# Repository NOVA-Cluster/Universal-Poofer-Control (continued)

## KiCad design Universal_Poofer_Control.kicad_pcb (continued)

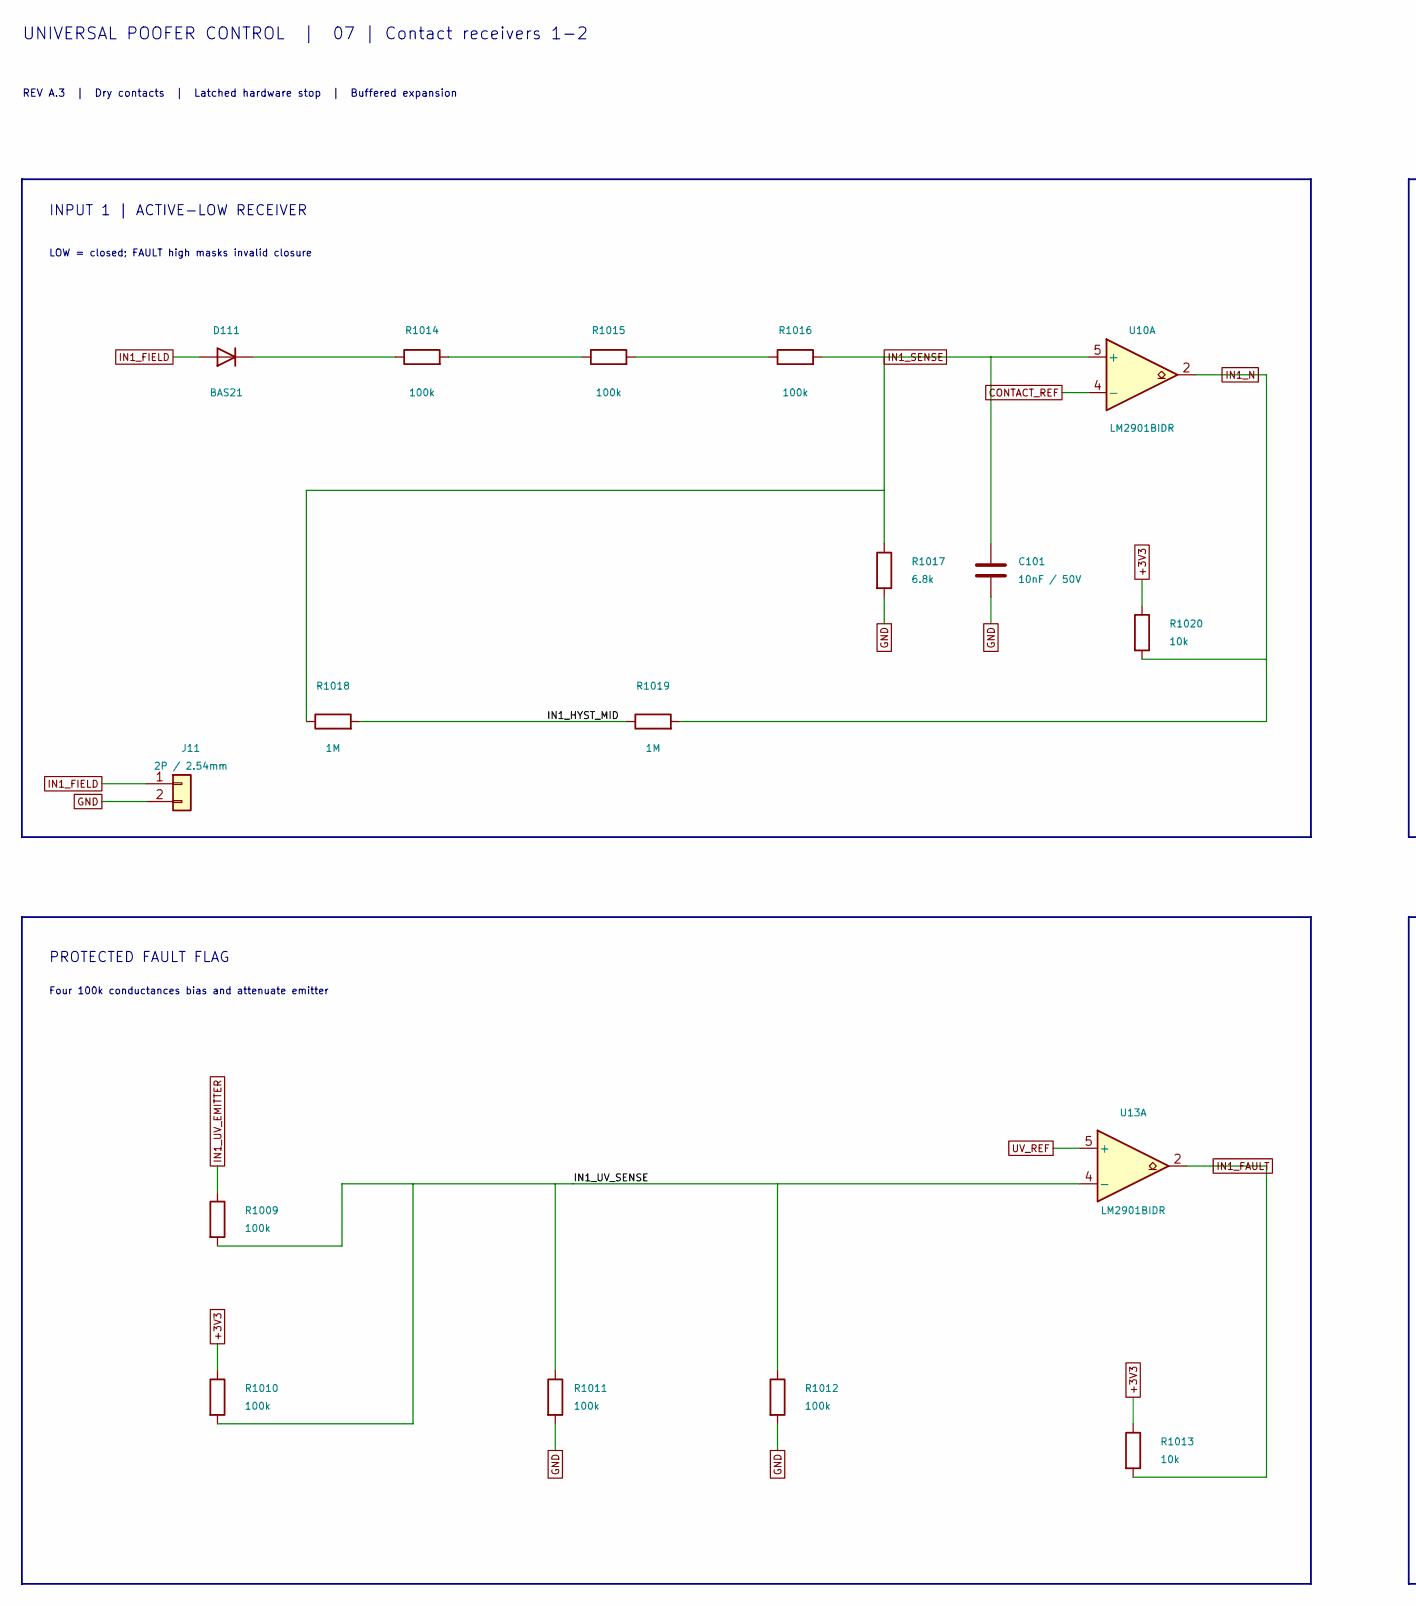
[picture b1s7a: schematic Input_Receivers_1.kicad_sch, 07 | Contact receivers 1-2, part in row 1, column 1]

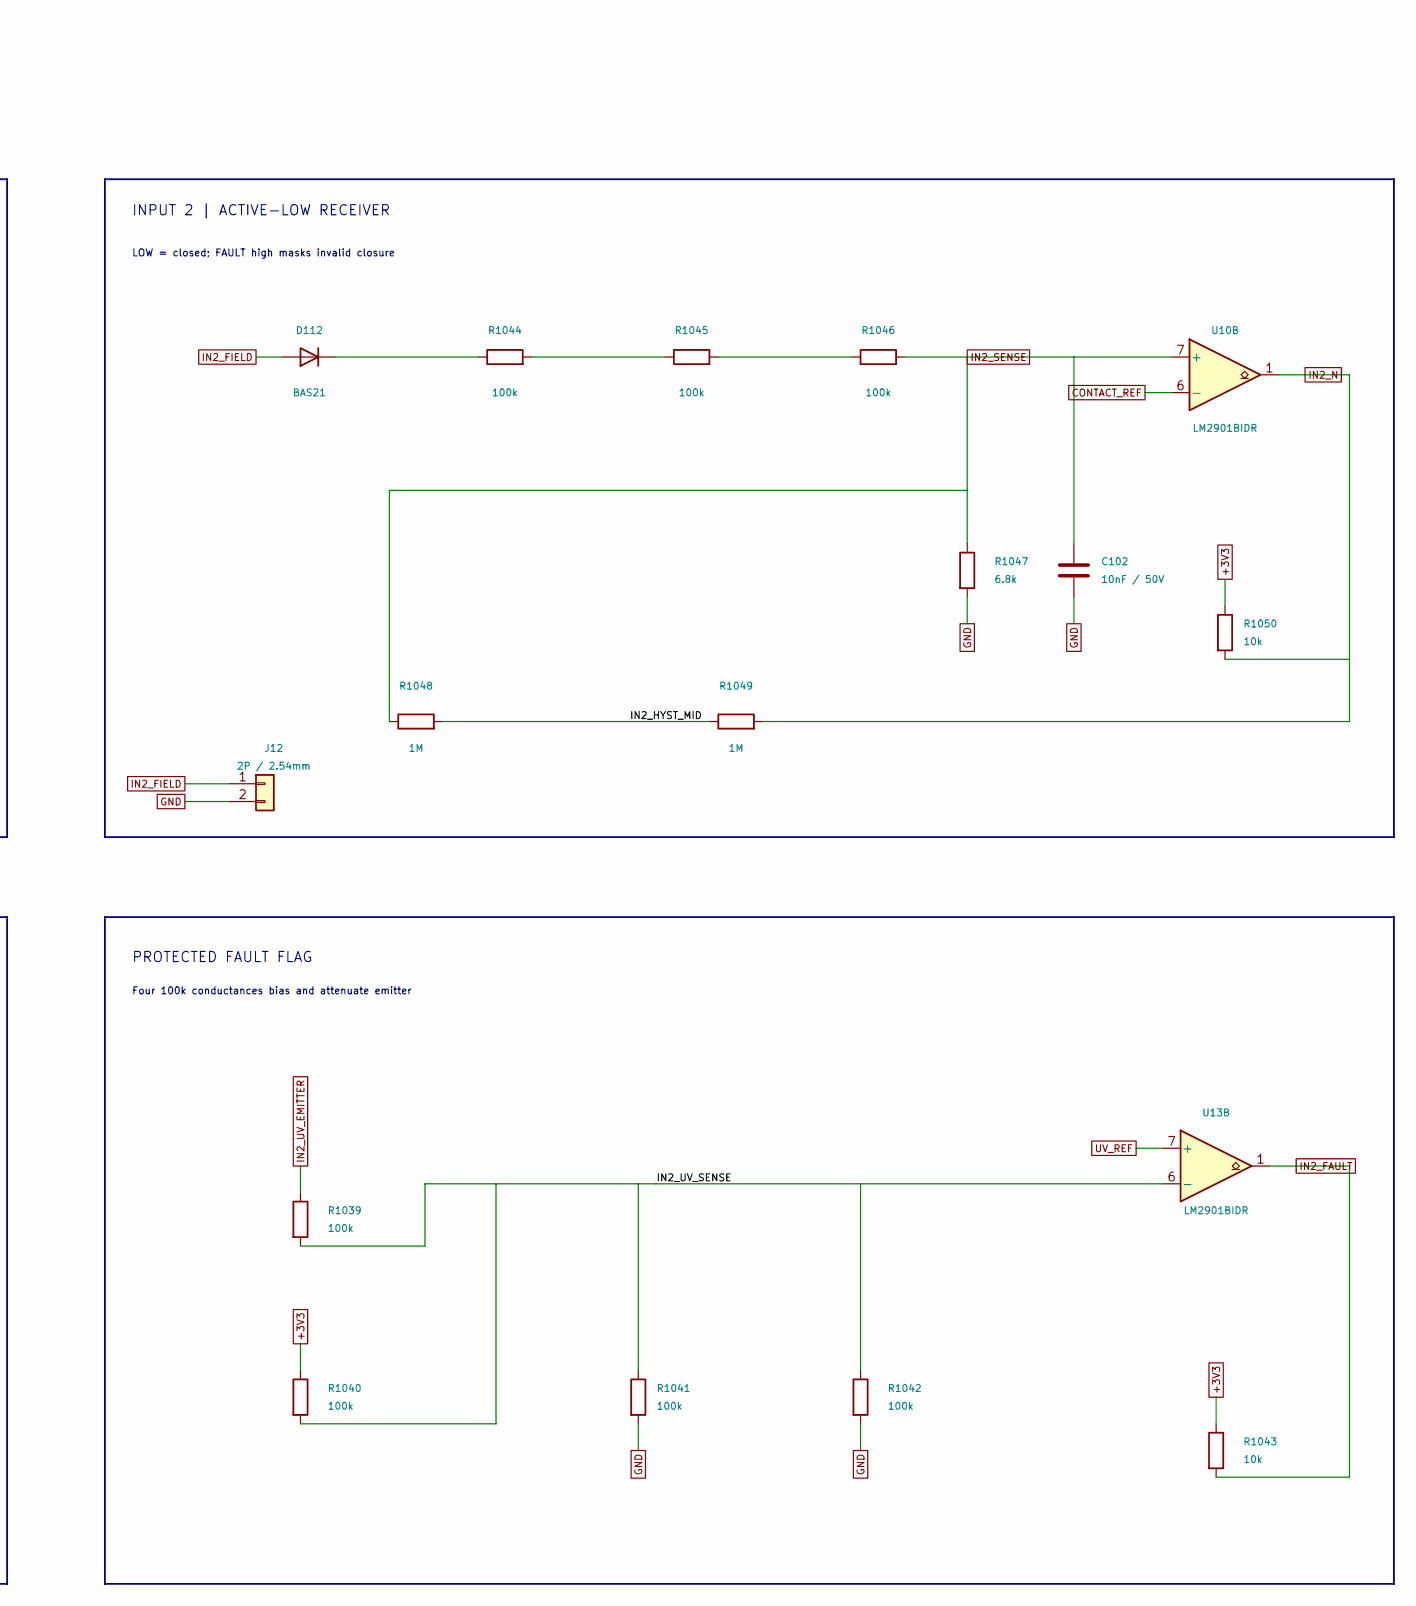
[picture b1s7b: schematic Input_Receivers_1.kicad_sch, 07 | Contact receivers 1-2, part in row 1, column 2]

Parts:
C101, C102: 10nF / 50V; C_0805_2012Metric; MPN CL21B103KBANNNC; LCSC C1710
D111, D112: BAS21; SOT-23; MPN BAS21,215; LCSC C8661
J11, J12: 2P / 2.54mm; PinHeader_1x02_P2.54mm_Vertical; MPN B-2100S02P-A110; LCSC C124375
R1009, R1010, R1011, R1012, R1014, R1015, R1016, R1039, R1040, R1041, R1042, R1044, R1045, R1046: 100k; R_0805_2012Metric; MPN 0805W8F1003T5E; LCSC C149504
R1013, R1020, R1043, R1050: 10k; R_0805_2012Metric; MPN 0805W8F1002T5E; LCSC C17414
R1017, R1047: 6.8k; R_0805_2012Metric; MPN 0805W8F6801T5E; LCSC C17772
R1018, R1019, R1048, R1049: 1M; R_0805_2012Metric; MPN 0805W8F1004T5E; LCSC C17514
U10, U13: LM2901BIDR; SOIC-14_3.9x8.7mm_P1.27mm; MPN LM2901BIDR; LCSC C22427890

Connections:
+3V3: R1010.1, R1013.1, R1020.1, R1040.1, R1043.1, R1050.1; also elsewhere on the board
/07 | Contact receivers 1-2/IN1_HYST_MID: R1018.2, R1019.1
/07 | Contact receivers 1-2/IN1_UV_SENSE: R1009.2, R1010.2, R1011.1, R1012.1, U13.4 (-)
/07 | Contact receivers 1-2/IN2_HYST_MID: R1048.2, R1049.1
/07 | Contact receivers 1-2/IN2_UV_SENSE: R1039.2, R1040.2, R1041.1, R1042.1, U13.6 (-)
CONTACT_REF: U10.4 (-), U10.6 (-); also elsewhere on the board
GND: C101.2, C102.2, J11.2, J12.2, R1011.2, R1012.2, R1017.2, R1041.2, R1042.2, R1047.2; also elsewhere on the board
IN1_FAULT: R1013.2, U13.2; also elsewhere on the board
IN1_FIELD: D111.1 (A), J11.1; also elsewhere on the board
IN1_N: R1019.2, R1020.2, U10.2; also elsewhere on the board
IN1_SENSE: C101.1, R1016.2, R1017.1, R1018.1, U10.5 (+)
IN1_UV_EMITTER: R1009.1; also elsewhere on the board
IN2_FAULT: R1043.2, U13.1; also elsewhere on the board
IN2_FIELD: D112.1 (A), J12.1; also elsewhere on the board
IN2_N: R1049.2, R1050.2, U10.1; also elsewhere on the board
IN2_SENSE: C102.1, R1046.2, R1047.1, R1048.1, U10.7 (+)
IN2_UV_EMITTER: R1039.1; also elsewhere on the board
unnamed: D111.3 (K), R1014.1
unnamed: D112.3 (K), R1044.1
unnamed: R1014.2, R1015.1
unnamed: R1015.2, R1016.1
unnamed: R1044.2, R1045.1
unnamed: R1045.2, R1046.1
UV_REF: U13.5 (+), U13.7 (+); also elsewhere on the board

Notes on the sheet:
UNIVERSAL POOFER CONTROL | 07 | Contact receivers 1-2
REV A.3 | Dry contacts | Latched hardware stop | Buffered expansion
INPUT 1 | ACTIVE-LOW RECEIVER
LOW = closed; FAULT high masks invalid closure
PROTECTED FAULT FLAG
Four 100k conductances bias and attenuate emitter
INPUT 2 | ACTIVE-LOW RECEIVER

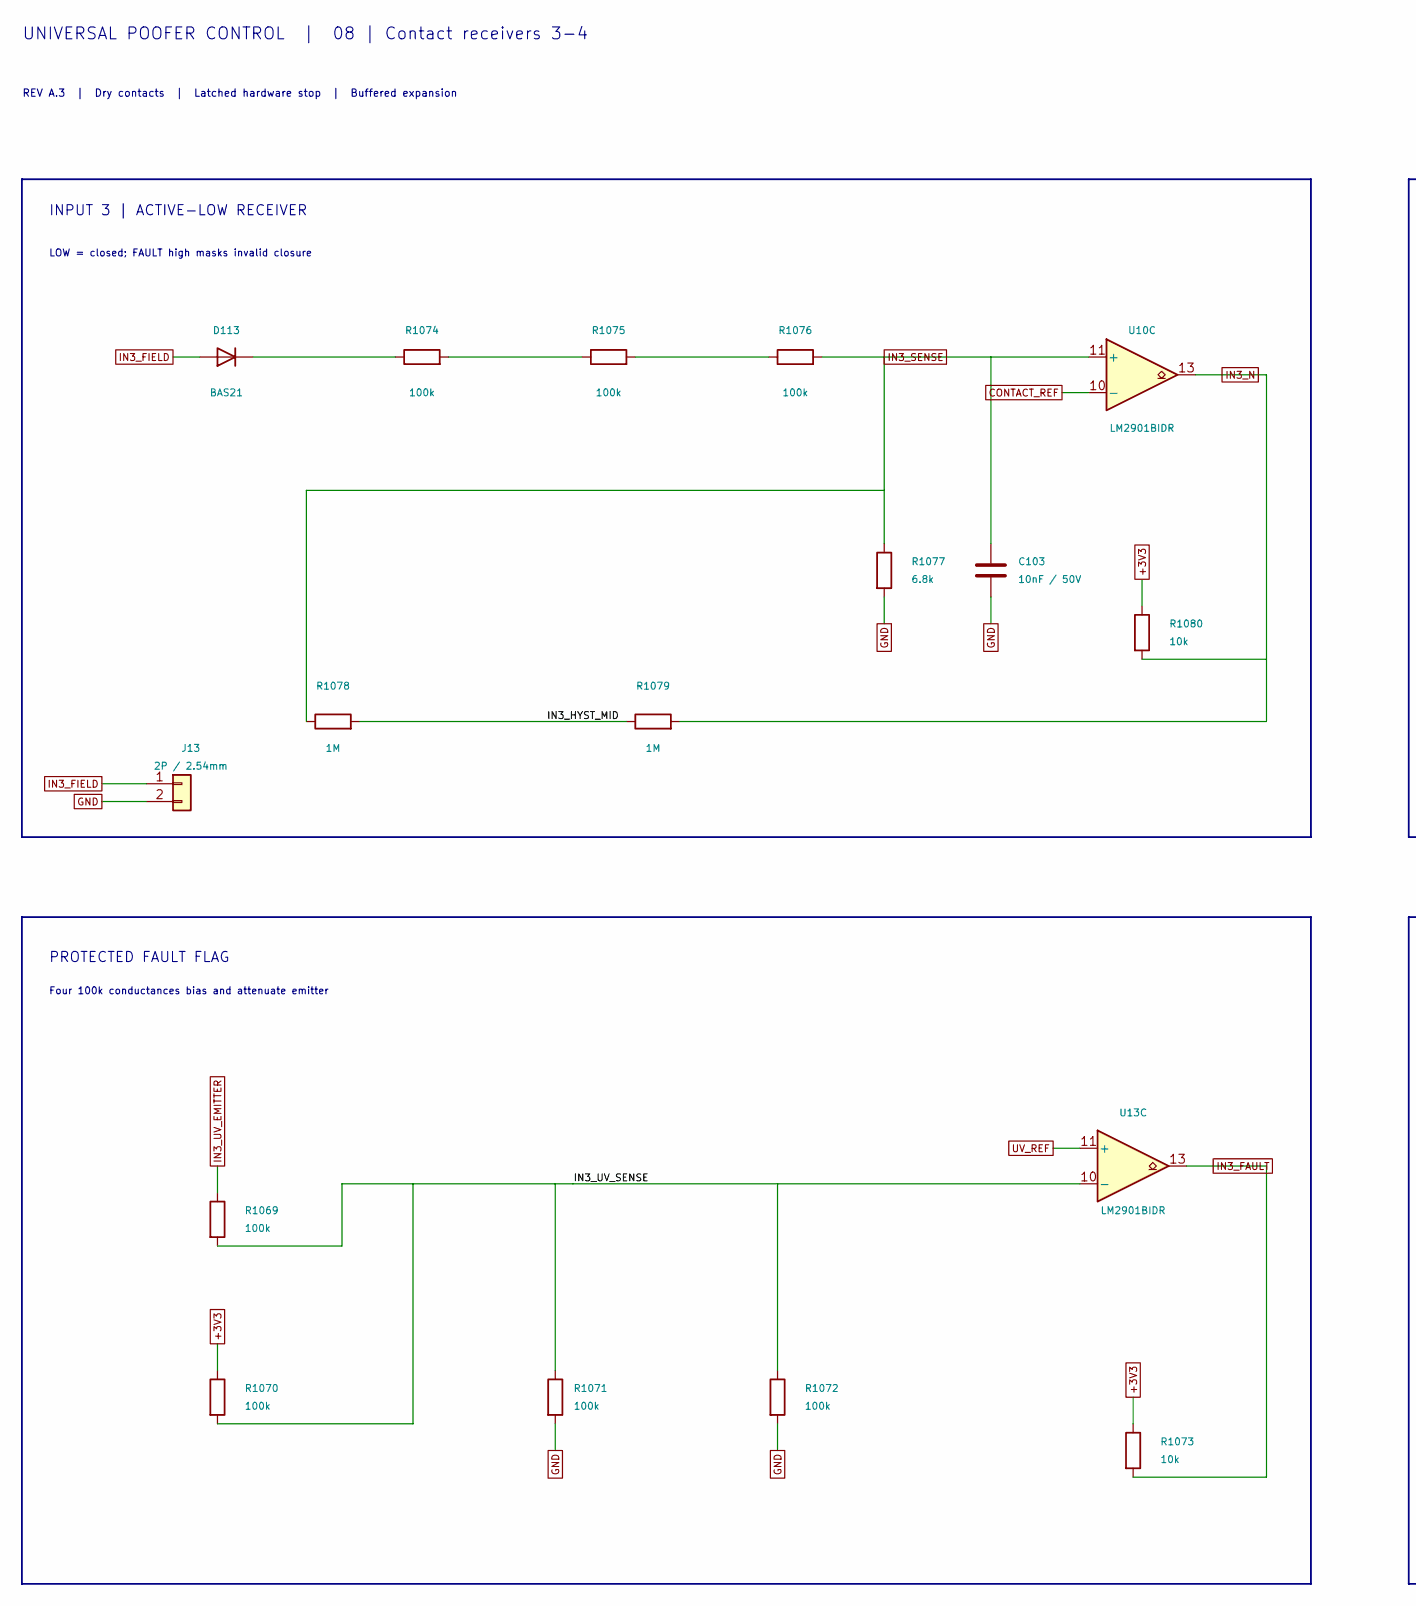
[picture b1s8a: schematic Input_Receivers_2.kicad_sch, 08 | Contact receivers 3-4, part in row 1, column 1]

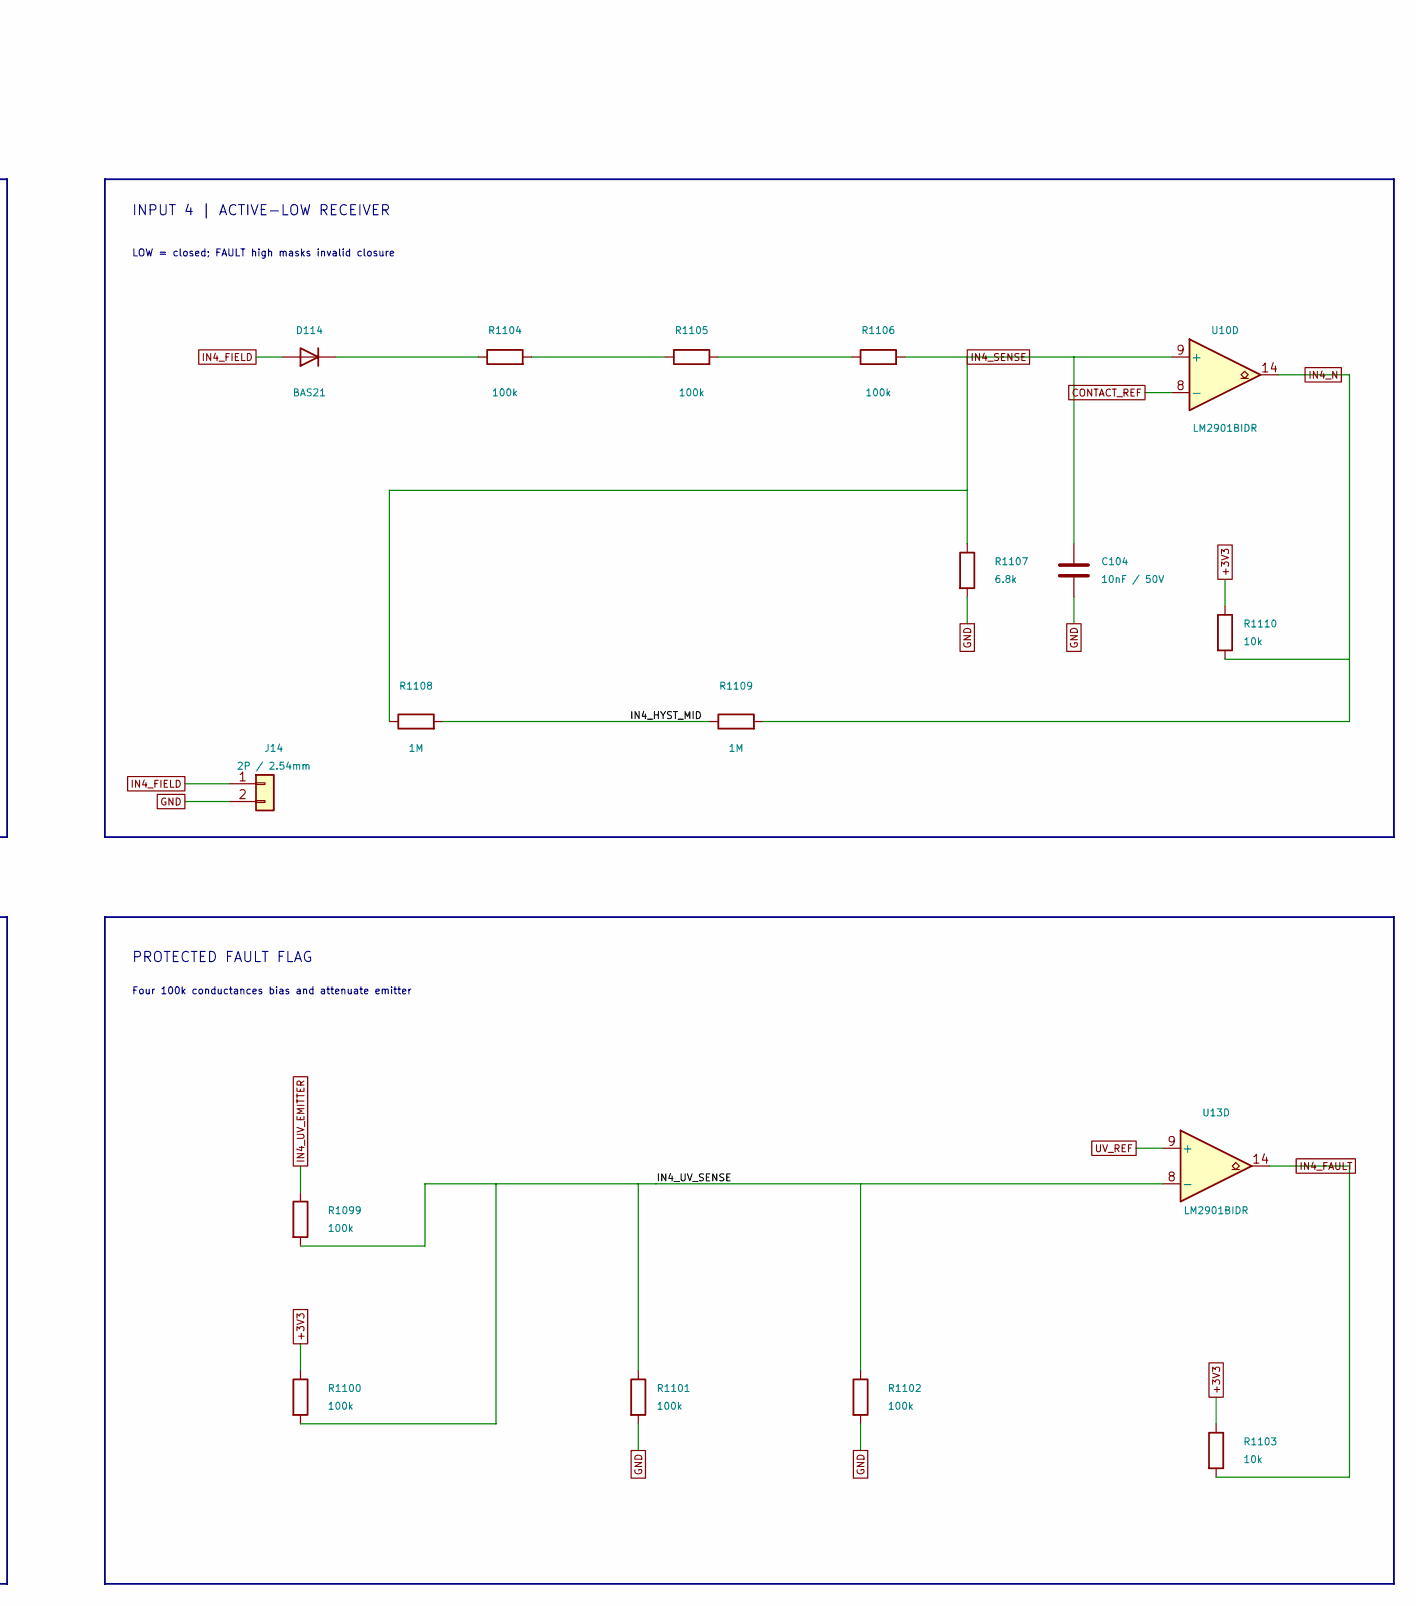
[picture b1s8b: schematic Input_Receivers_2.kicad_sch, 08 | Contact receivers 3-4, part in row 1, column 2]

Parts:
C103, C104: 10nF / 50V; C_0805_2012Metric; MPN CL21B103KBANNNC; LCSC C1710
D113, D114: BAS21; SOT-23; MPN BAS21,215; LCSC C8661
J13, J14: 2P / 2.54mm; PinHeader_1x02_P2.54mm_Vertical; MPN B-2100S02P-A110; LCSC C124375
R1069, R1070, R1071, R1072, R1074, R1075, R1076, R1099, R1100, R1101, R1102, R1104, R1105, R1106: 100k; R_0805_2012Metric; MPN 0805W8F1003T5E; LCSC C149504
R1073, R1080, R1103, R1110: 10k; R_0805_2012Metric; MPN 0805W8F1002T5E; LCSC C17414
R1077, R1107: 6.8k; R_0805_2012Metric; MPN 0805W8F6801T5E; LCSC C17772
R1078, R1079, R1108, R1109: 1M; R_0805_2012Metric; MPN 0805W8F1004T5E; LCSC C17514
U10, U13: LM2901BIDR; SOIC-14_3.9x8.7mm_P1.27mm; MPN LM2901BIDR; LCSC C22427890

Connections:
+3V3: R1070.1, R1073.1, R1080.1, R1100.1, R1103.1, R1110.1; also elsewhere on the board
/08 | Contact receivers 3-4/IN3_HYST_MID: R1078.2, R1079.1
/08 | Contact receivers 3-4/IN3_UV_SENSE: R1069.2, R1070.2, R1071.1, R1072.1, U13.10 (-)
/08 | Contact receivers 3-4/IN4_HYST_MID: R1108.2, R1109.1
/08 | Contact receivers 3-4/IN4_UV_SENSE: R1099.2, R1100.2, R1101.1, R1102.1, U13.8 (-)
CONTACT_REF: U10.8 (-), U10.10 (-); also elsewhere on the board
GND: C103.2, C104.2, J13.2, J14.2, R1071.2, R1072.2, R1077.2, R1101.2, R1102.2, R1107.2; also elsewhere on the board
IN3_FAULT: R1073.2, U13.13; also elsewhere on the board
IN3_FIELD: D113.1 (A), J13.1; also elsewhere on the board
IN3_N: R1079.2, R1080.2, U10.13; also elsewhere on the board
IN3_SENSE: C103.1, R1076.2, R1077.1, R1078.1, U10.11 (+)
IN3_UV_EMITTER: R1069.1; also elsewhere on the board
IN4_FAULT: R1103.2, U13.14; also elsewhere on the board
IN4_FIELD: D114.1 (A), J14.1; also elsewhere on the board
IN4_N: R1109.2, R1110.2, U10.14; also elsewhere on the board
IN4_SENSE: C104.1, R1106.2, R1107.1, R1108.1, U10.9 (+)
IN4_UV_EMITTER: R1099.1; also elsewhere on the board
unnamed: D113.3 (K), R1074.1
unnamed: D114.3 (K), R1104.1
unnamed: R1074.2, R1075.1
unnamed: R1075.2, R1076.1
unnamed: R1104.2, R1105.1
unnamed: R1105.2, R1106.1
UV_REF: U13.9 (+), U13.11 (+); also elsewhere on the board

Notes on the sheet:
UNIVERSAL POOFER CONTROL | 08 | Contact receivers 3-4
REV A.3 | Dry contacts | Latched hardware stop | Buffered expansion
INPUT 3 | ACTIVE-LOW RECEIVER
LOW = closed; FAULT high masks invalid closure
PROTECTED FAULT FLAG
Four 100k conductances bias and attenuate emitter
INPUT 4 | ACTIVE-LOW RECEIVER

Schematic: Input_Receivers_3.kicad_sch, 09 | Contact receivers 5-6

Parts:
C105, C106: 10nF / 50V; C_0805_2012Metric; MPN CL21B103KBANNNC; LCSC C1710
D115, D116: BAS21; SOT-23; MPN BAS21,215; LCSC C8661
J15, J16: 2P / 2.54mm; PinHeader_1x02_P2.54mm_Vertical; MPN B-2100S02P-A110; LCSC C124375
R1129, R1130, R1131, R1132, R1134, R1135, R1136, R1159, R1160, R1161, R1162, R1164, R1165, R1166: 100k; R_0805_2012Metric; MPN 0805W8F1003T5E; LCSC C149504
R1133, R1140, R1163, R1170: 10k; R_0805_2012Metric; MPN 0805W8F1002T5E; LCSC C17414
R1137, R1167: 6.8k; R_0805_2012Metric; MPN 0805W8F6801T5E; LCSC C17772
R1138, R1139, R1168, R1169: 1M; R_0805_2012Metric; MPN 0805W8F1004T5E; LCSC C17514
U11, U14: LM2901BIDR; SOIC-14_3.9x8.7mm_P1.27mm; MPN LM2901BIDR; LCSC C22427890

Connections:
+3V3: R1130.1, R1133.1, R1140.1, R1160.1, R1163.1, R1170.1; also elsewhere on the board
/09 | Contact receivers 5-6/IN5_HYST_MID: R1138.2, R1139.1
/09 | Contact receivers 5-6/IN5_UV_SENSE: R1129.2, R1130.2, R1131.1, R1132.1, U14.4 (-)
/09 | Contact receivers 5-6/IN6_HYST_MID: R1168.2, R1169.1
/09 | Contact receivers 5-6/IN6_UV_SENSE: R1159.2, R1160.2, R1161.1, R1162.1, U14.6 (-)
CONTACT_REF: U11.4 (-), U11.6 (-); also elsewhere on the board
GND: C105.2, C106.2, J15.2, J16.2, R1131.2, R1132.2, R1137.2, R1161.2, R1162.2, R1167.2; also elsewhere on the board
IN5_FAULT: R1133.2, U14.2; also elsewhere on the board
IN5_FIELD: D115.1 (A), J15.1; also elsewhere on the board
IN5_N: R1139.2, R1140.2, U11.2; also elsewhere on the board
IN5_SENSE: C105.1, R1136.2, R1137.1, R1138.1, U11.5 (+)
IN5_UV_EMITTER: R1129.1; also elsewhere on the board
IN6_FAULT: R1163.2, U14.1; also elsewhere on the board
IN6_FIELD: D116.1 (A), J16.1; also elsewhere on the board
IN6_N: R1169.2, R1170.2, U11.1; also elsewhere on the board
IN6_SENSE: C106.1, R1166.2, R1167.1, R1168.1, U11.7 (+)
IN6_UV_EMITTER: R1159.1; also elsewhere on the board
unnamed: D115.3 (K), R1134.1
unnamed: D116.3 (K), R1164.1
unnamed: R1134.2, R1135.1
unnamed: R1135.2, R1136.1
unnamed: R1164.2, R1165.1
unnamed: R1165.2, R1166.1
UV_REF: U14.5 (+), U14.7 (+); also elsewhere on the board

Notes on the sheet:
UNIVERSAL POOFER CONTROL | 09 | Contact receivers 5-6
REV A.3 | Dry contacts | Latched hardware stop | Buffered expansion
INPUT 5 | ACTIVE-LOW RECEIVER
LOW = closed; FAULT high masks invalid closure
PROTECTED FAULT FLAG
Four 100k conductances bias and attenuate emitter
INPUT 6 | ACTIVE-LOW RECEIVER

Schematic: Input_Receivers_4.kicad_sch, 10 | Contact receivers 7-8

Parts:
C107, C108: 10nF / 50V; C_0805_2012Metric; MPN CL21B103KBANNNC; LCSC C1710
D117, D118: BAS21; SOT-23; MPN BAS21,215; LCSC C8661
J17, J18: 2P / 2.54mm; PinHeader_1x02_P2.54mm_Vertical; MPN B-2100S02P-A110; LCSC C124375
R1189, R1190, R1191, R1192, R1194, R1195, R1196, R1219, R1220, R1221, R1222, R1224, R1225, R1226: 100k; R_0805_2012Metric; MPN 0805W8F1003T5E; LCSC C149504
R1193, R1200, R1223, R1230: 10k; R_0805_2012Metric; MPN 0805W8F1002T5E; LCSC C17414
R1197, R1227: 6.8k; R_0805_2012Metric; MPN 0805W8F6801T5E; LCSC C17772
R1198, R1199, R1228, R1229: 1M; R_0805_2012Metric; MPN 0805W8F1004T5E; LCSC C17514
U11, U14: LM2901BIDR; SOIC-14_3.9x8.7mm_P1.27mm; MPN LM2901BIDR; LCSC C22427890

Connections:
+3V3: R1190.1, R1193.1, R1200.1, R1220.1, R1223.1, R1230.1; also elsewhere on the board
/10 | Contact receivers 7-8/IN7_HYST_MID: R1198.2, R1199.1
/10 | Contact receivers 7-8/IN7_UV_SENSE: R1189.2, R1190.2, R1191.1, R1192.1, U14.10 (-)
/10 | Contact receivers 7-8/IN8_HYST_MID: R1228.2, R1229.1
/10 | Contact receivers 7-8/IN8_UV_SENSE: R1219.2, R1220.2, R1221.1, R1222.1, U14.8 (-)
CONTACT_REF: U11.8 (-), U11.10 (-); also elsewhere on the board
GND: C107.2, C108.2, J17.2, J18.2, R1191.2, R1192.2, R1197.2, R1221.2, R1222.2, R1227.2; also elsewhere on the board
IN7_FAULT: R1193.2, U14.13; also elsewhere on the board
IN7_FIELD: D117.1 (A), J17.1; also elsewhere on the board
IN7_N: R1199.2, R1200.2, U11.13; also elsewhere on the board
IN7_SENSE: C107.1, R1196.2, R1197.1, R1198.1, U11.11 (+)
IN7_UV_EMITTER: R1189.1; also elsewhere on the board
IN8_FAULT: R1223.2, U14.14; also elsewhere on the board
IN8_FIELD: D118.1 (A), J18.1; also elsewhere on the board
IN8_N: R1229.2, R1230.2, U11.14; also elsewhere on the board
IN8_SENSE: C108.1, R1226.2, R1227.1, R1228.1, U11.9 (+)
IN8_UV_EMITTER: R1219.1; also elsewhere on the board
unnamed: D117.3 (K), R1194.1
unnamed: D118.3 (K), R1224.1
unnamed: R1194.2, R1195.1
unnamed: R1195.2, R1196.1
unnamed: R1224.2, R1225.1
unnamed: R1225.2, R1226.1
UV_REF: U14.9 (+), U14.11 (+); also elsewhere on the board

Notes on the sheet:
UNIVERSAL POOFER CONTROL | 10 | Contact receivers 7-8
REV A.3 | Dry contacts | Latched hardware stop | Buffered expansion
INPUT 7 | ACTIVE-LOW RECEIVER
LOW = closed; FAULT high masks invalid closure
PROTECTED FAULT FLAG
Four 100k conductances bias and attenuate emitter
INPUT 8 | ACTIVE-LOW RECEIVER

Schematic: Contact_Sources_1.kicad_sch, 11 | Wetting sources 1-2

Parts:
C131, C132: 100nF; C_0805_2012Metric; MPN CC0805KRX7R9BB104; LCSC C49678
C161, C162: 1nF / 50V; C_0805_2012Metric; MPN CL21B102KBANNNC; LCSC C51210
D101, D102, D121, D122: BAS21; SOT-23; MPN BAS21,215; LCSC C8661
D141, D142: BAT54; SOT-23; MPN BAT54,215; LCSC C85084
Q101, Q102: MJD350T4G; TO-252-3_TabPin2; MPN MJD350T4G; LCSC C145514
Q111, Q112, Q121, Q122: MMBT3904; SOT-23; MPN MMBT3904(RANGE:100-300); LCSC C20526
Q131, Q132: AO3401A; SOT-23; MPN AO3401A; LCSC C15127
Q151, Q152: MMBT3906; SOT-23; MPN MMBT3906 2A(RANGE:100-300); LCSC C2143
R1000, R1030: 33R; R_0805_2012Metric; MPN 0805W8F330JT5E; LCSC C17634
R1001, R1031: 2.2k; R_0805_2012Metric; MPN 0805W8F2201T5E; LCSC C17520
R1002, R1003, R1022, R1023, R1032, R1033, R1052, R1053: 1k; R_0805_2012Metric; MPN 0805W8F1001T5E; LCSC C17513
R1004, R1005, R1006, R1007, R1034, R1035, R1036, R1037: 100k; R_0805_2012Metric; MPN 0805W8F1003T5E; LCSC C149504
R1008, R1038: 68k; R_0805_2012Metric; MPN 0805W8F6802T5E; LCSC C17801
R1021, R1051: 10k; R_0805_2012Metric; MPN 0805W8F1002T5E; LCSC C17414
U20: LM2902DR; SOIC-14_3.9x8.7mm_P1.27mm; MPN LM2902DR; LCSC C350545

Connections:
+5V_LOGIC: Q131.2 (S), Q132.2 (S), Q151.2 (E), Q152.2 (E), R1000.1, R1003.1, R1008.1, R1022.1, R1030.1, R1033.1, R1038.1, R1052.1; also elsewhere on the board
/11 | Wetting sources 1-2/IN1_AMP_OUT: C131.1, R1001.2, U20.1
/11 | Wetting sources 1-2/IN1_DRV_BASE: Q111.1 (B), R1001.1
/11 | Wetting sources 1-2/IN1_DRV_COL: Q111.3 (C), R1002.2
/11 | Wetting sources 1-2/IN1_UV_GATE: Q121.3 (C), Q131.1 (G), R1008.2
/11 | Wetting sources 1-2/IN1_WET_COLLECTOR: D101.1 (A), Q101.2 (C)
/11 | Wetting sources 1-2/IN2_AMP_OUT: C132.1, R1031.2, U20.7
/11 | Wetting sources 1-2/IN2_DRV_BASE: Q112.1 (B), R1031.1
/11 | Wetting sources 1-2/IN2_DRV_COL: Q112.3 (C), R1032.2
/11 | Wetting sources 1-2/IN2_UV_GATE: Q122.3 (C), Q132.1 (G), R1038.2
/11 | Wetting sources 1-2/IN2_WET_COLLECTOR: D102.1 (A), Q102.2 (C)
CURRENT_REF: D141.1 (A), D142.1 (A), R1021.1, R1051.1; also elsewhere on the board
GND: C161.2, C162.2, Q111.2 (E), Q112.2 (E), Q121.1 (B), Q122.1 (B), R1007.2, R1037.2; also elsewhere on the board
IN1_AMP_REF: C131.2, D141.3 (K), R1021.2, U20.2 (-)
IN1_EMIT_F: U20.3 (+); also elsewhere on the board
IN1_FIELD: D101.3 (K), D121.3 (K); also elsewhere on the board
IN1_LIMIT_BASE: Q151.1 (B), R1022.2, R1023.1
IN1_UV_EMITTER: C161.1, Q121.2 (E), R1004.1, R1007.1; also elsewhere on the board
IN1_WET_BASE: Q101.1 (B), Q131.3 (D), Q151.3 (C), R1002.1, R1003.2
IN1_WET_EMIT: Q101.3 (E), R1000.2, R1023.2; also elsewhere on the board
IN2_AMP_REF: C132.2, D142.3 (K), R1051.2, U20.6 (-)
IN2_EMIT_F: U20.5 (+); also elsewhere on the board
IN2_FIELD: D102.3 (K), D122.3 (K); also elsewhere on the board
IN2_LIMIT_BASE: Q152.1 (B), R1052.2, R1053.1
IN2_UV_EMITTER: C162.1, Q122.2 (E), R1034.1, R1037.1; also elsewhere on the board
IN2_WET_BASE: Q102.1 (B), Q132.3 (D), Q152.3 (C), R1032.1, R1033.2
IN2_WET_EMIT: Q102.3 (E), R1030.2, R1053.2; also elsewhere on the board
unnamed: D121.1 (A), R1006.2
unnamed: D122.1 (A), R1036.2
unnamed: R1004.2, R1005.1
unnamed: R1005.2, R1006.1
unnamed: R1034.2, R1035.1
unnamed: R1035.2, R1036.1

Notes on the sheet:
UNIVERSAL POOFER CONTROL | 11 | Wetting sources 1-2
REV A.3 | Dry contacts | Latched hardware stop | Buffered expansion
INPUT 1 | PRECISION WETTING SOURCE
Nominal 20 mA; compensated servo and backup limiter
AUTONOMOUS NEGATIVE-FAULT CLAMP
INPUT 2 | PRECISION WETTING SOURCE

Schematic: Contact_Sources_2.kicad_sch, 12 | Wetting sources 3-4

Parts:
C133, C134: 100nF; C_0805_2012Metric; MPN CC0805KRX7R9BB104; LCSC C49678
C163, C164: 1nF / 50V; C_0805_2012Metric; MPN CL21B102KBANNNC; LCSC C51210
D103, D104, D123, D124: BAS21; SOT-23; MPN BAS21,215; LCSC C8661
D143, D144: BAT54; SOT-23; MPN BAT54,215; LCSC C85084
Q103, Q104: MJD350T4G; TO-252-3_TabPin2; MPN MJD350T4G; LCSC C145514
Q113, Q114, Q123, Q124: MMBT3904; SOT-23; MPN MMBT3904(RANGE:100-300); LCSC C20526
Q133, Q134: AO3401A; SOT-23; MPN AO3401A; LCSC C15127
Q153, Q154: MMBT3906; SOT-23; MPN MMBT3906 2A(RANGE:100-300); LCSC C2143
R1060, R1090: 33R; R_0805_2012Metric; MPN 0805W8F330JT5E; LCSC C17634
R1061, R1091: 2.2k; R_0805_2012Metric; MPN 0805W8F2201T5E; LCSC C17520
R1062, R1063, R1082, R1083, R1092, R1093, R1112, R1113: 1k; R_0805_2012Metric; MPN 0805W8F1001T5E; LCSC C17513
R1064, R1065, R1066, R1067, R1094, R1095, R1096, R1097: 100k; R_0805_2012Metric; MPN 0805W8F1003T5E; LCSC C149504
R1068, R1098: 68k; R_0805_2012Metric; MPN 0805W8F6802T5E; LCSC C17801
R1081, R1111: 10k; R_0805_2012Metric; MPN 0805W8F1002T5E; LCSC C17414
U20: LM2902DR; SOIC-14_3.9x8.7mm_P1.27mm; MPN LM2902DR; LCSC C350545

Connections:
+5V_LOGIC: Q133.2 (S), Q134.2 (S), Q153.2 (E), Q154.2 (E), R1060.1, R1063.1, R1068.1, R1082.1, R1090.1, R1093.1, R1098.1, R1112.1; also elsewhere on the board
/12 | Wetting sources 3-4/IN3_AMP_OUT: C133.1, R1061.2, U20.8
/12 | Wetting sources 3-4/IN3_DRV_BASE: Q113.1 (B), R1061.1
/12 | Wetting sources 3-4/IN3_DRV_COL: Q113.3 (C), R1062.2
/12 | Wetting sources 3-4/IN3_UV_GATE: Q123.3 (C), Q133.1 (G), R1068.2
/12 | Wetting sources 3-4/IN3_WET_COLLECTOR: D103.1 (A), Q103.2 (C)
/12 | Wetting sources 3-4/IN4_AMP_OUT: C134.1, R1091.2, U20.14
/12 | Wetting sources 3-4/IN4_DRV_BASE: Q114.1 (B), R1091.1
/12 | Wetting sources 3-4/IN4_DRV_COL: Q114.3 (C), R1092.2
/12 | Wetting sources 3-4/IN4_UV_GATE: Q124.3 (C), Q134.1 (G), R1098.2
/12 | Wetting sources 3-4/IN4_WET_COLLECTOR: D104.1 (A), Q104.2 (C)
CURRENT_REF: D143.1 (A), D144.1 (A), R1081.1, R1111.1; also elsewhere on the board
GND: C163.2, C164.2, Q113.2 (E), Q114.2 (E), Q123.1 (B), Q124.1 (B), R1067.2, R1097.2; also elsewhere on the board
IN3_AMP_REF: C133.2, D143.3 (K), R1081.2, U20.9 (-)
IN3_EMIT_F: U20.10 (+); also elsewhere on the board
IN3_FIELD: D103.3 (K), D123.3 (K); also elsewhere on the board
IN3_LIMIT_BASE: Q153.1 (B), R1082.2, R1083.1
IN3_UV_EMITTER: C163.1, Q123.2 (E), R1064.1, R1067.1; also elsewhere on the board
IN3_WET_BASE: Q103.1 (B), Q133.3 (D), Q153.3 (C), R1062.1, R1063.2
IN3_WET_EMIT: Q103.3 (E), R1060.2, R1083.2; also elsewhere on the board
IN4_AMP_REF: C134.2, D144.3 (K), R1111.2, U20.13 (-)
IN4_EMIT_F: U20.12 (+); also elsewhere on the board
IN4_FIELD: D104.3 (K), D124.3 (K); also elsewhere on the board
IN4_LIMIT_BASE: Q154.1 (B), R1112.2, R1113.1
IN4_UV_EMITTER: C164.1, Q124.2 (E), R1094.1, R1097.1; also elsewhere on the board
IN4_WET_BASE: Q104.1 (B), Q134.3 (D), Q154.3 (C), R1092.1, R1093.2
IN4_WET_EMIT: Q104.3 (E), R1090.2, R1113.2; also elsewhere on the board
unnamed: D123.1 (A), R1066.2
unnamed: D124.1 (A), R1096.2
unnamed: R1064.2, R1065.1
unnamed: R1065.2, R1066.1
unnamed: R1094.2, R1095.1
unnamed: R1095.2, R1096.1

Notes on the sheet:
UNIVERSAL POOFER CONTROL | 12 | Wetting sources 3-4
REV A.3 | Dry contacts | Latched hardware stop | Buffered expansion
INPUT 3 | PRECISION WETTING SOURCE
Nominal 20 mA; compensated servo and backup limiter
AUTONOMOUS NEGATIVE-FAULT CLAMP
INPUT 4 | PRECISION WETTING SOURCE

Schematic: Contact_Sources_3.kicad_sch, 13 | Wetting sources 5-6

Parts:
C135, C136: 100nF; C_0805_2012Metric; MPN CC0805KRX7R9BB104; LCSC C49678
C165, C166: 1nF / 50V; C_0805_2012Metric; MPN CL21B102KBANNNC; LCSC C51210
D105, D106, D125, D126: BAS21; SOT-23; MPN BAS21,215; LCSC C8661
D145, D146: BAT54; SOT-23; MPN BAT54,215; LCSC C85084
Q105, Q106: MJD350T4G; TO-252-3_TabPin2; MPN MJD350T4G; LCSC C145514
Q115, Q116, Q125, Q126: MMBT3904; SOT-23; MPN MMBT3904(RANGE:100-300); LCSC C20526
Q135, Q136: AO3401A; SOT-23; MPN AO3401A; LCSC C15127
Q155, Q156: MMBT3906; SOT-23; MPN MMBT3906 2A(RANGE:100-300); LCSC C2143
R1120, R1150: 33R; R_0805_2012Metric; MPN 0805W8F330JT5E; LCSC C17634
R1121, R1151: 2.2k; R_0805_2012Metric; MPN 0805W8F2201T5E; LCSC C17520
R1122, R1123, R1142, R1143, R1152, R1153, R1172, R1173: 1k; R_0805_2012Metric; MPN 0805W8F1001T5E; LCSC C17513
R1124, R1125, R1126, R1127, R1154, R1155, R1156, R1157: 100k; R_0805_2012Metric; MPN 0805W8F1003T5E; LCSC C149504
R1128, R1158: 68k; R_0805_2012Metric; MPN 0805W8F6802T5E; LCSC C17801
R1141, R1171: 10k; R_0805_2012Metric; MPN 0805W8F1002T5E; LCSC C17414
U21: LM2902DR; SOIC-14_3.9x8.7mm_P1.27mm; MPN LM2902DR; LCSC C350545

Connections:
+5V_LOGIC: Q135.2 (S), Q136.2 (S), Q155.2 (E), Q156.2 (E), R1120.1, R1123.1, R1128.1, R1142.1, R1150.1, R1153.1, R1158.1, R1172.1; also elsewhere on the board
/13 | Wetting sources 5-6/IN5_AMP_OUT: C135.1, R1121.2, U21.1
/13 | Wetting sources 5-6/IN5_DRV_BASE: Q115.1 (B), R1121.1
/13 | Wetting sources 5-6/IN5_DRV_COL: Q115.3 (C), R1122.2
/13 | Wetting sources 5-6/IN5_UV_GATE: Q125.3 (C), Q135.1 (G), R1128.2
/13 | Wetting sources 5-6/IN5_WET_COLLECTOR: D105.1 (A), Q105.2 (C)
/13 | Wetting sources 5-6/IN6_AMP_OUT: C136.1, R1151.2, U21.7
/13 | Wetting sources 5-6/IN6_DRV_BASE: Q116.1 (B), R1151.1
/13 | Wetting sources 5-6/IN6_DRV_COL: Q116.3 (C), R1152.2
/13 | Wetting sources 5-6/IN6_UV_GATE: Q126.3 (C), Q136.1 (G), R1158.2
/13 | Wetting sources 5-6/IN6_WET_COLLECTOR: D106.1 (A), Q106.2 (C)
CURRENT_REF: D145.1 (A), D146.1 (A), R1141.1, R1171.1; also elsewhere on the board
GND: C165.2, C166.2, Q115.2 (E), Q116.2 (E), Q125.1 (B), Q126.1 (B), R1127.2, R1157.2; also elsewhere on the board
IN5_AMP_REF: C135.2, D145.3 (K), R1141.2, U21.2 (-)
IN5_EMIT_F: U21.3 (+); also elsewhere on the board
IN5_FIELD: D105.3 (K), D125.3 (K); also elsewhere on the board
IN5_LIMIT_BASE: Q155.1 (B), R1142.2, R1143.1
IN5_UV_EMITTER: C165.1, Q125.2 (E), R1124.1, R1127.1; also elsewhere on the board
IN5_WET_BASE: Q105.1 (B), Q135.3 (D), Q155.3 (C), R1122.1, R1123.2
IN5_WET_EMIT: Q105.3 (E), R1120.2, R1143.2; also elsewhere on the board
IN6_AMP_REF: C136.2, D146.3 (K), R1171.2, U21.6 (-)
IN6_EMIT_F: U21.5 (+); also elsewhere on the board
IN6_FIELD: D106.3 (K), D126.3 (K); also elsewhere on the board
IN6_LIMIT_BASE: Q156.1 (B), R1172.2, R1173.1
IN6_UV_EMITTER: C166.1, Q126.2 (E), R1154.1, R1157.1; also elsewhere on the board
IN6_WET_BASE: Q106.1 (B), Q136.3 (D), Q156.3 (C), R1152.1, R1153.2
IN6_WET_EMIT: Q106.3 (E), R1150.2, R1173.2; also elsewhere on the board
unnamed: D125.1 (A), R1126.2
unnamed: D126.1 (A), R1156.2
unnamed: R1124.2, R1125.1
unnamed: R1125.2, R1126.1
unnamed: R1154.2, R1155.1
unnamed: R1155.2, R1156.1

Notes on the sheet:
UNIVERSAL POOFER CONTROL | 13 | Wetting sources 5-6
REV A.3 | Dry contacts | Latched hardware stop | Buffered expansion
INPUT 5 | PRECISION WETTING SOURCE
Nominal 20 mA; compensated servo and backup limiter
AUTONOMOUS NEGATIVE-FAULT CLAMP
INPUT 6 | PRECISION WETTING SOURCE

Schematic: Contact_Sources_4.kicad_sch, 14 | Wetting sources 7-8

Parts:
C137, C138: 100nF; C_0805_2012Metric; MPN CC0805KRX7R9BB104; LCSC C49678
C167, C168: 1nF / 50V; C_0805_2012Metric; MPN CL21B102KBANNNC; LCSC C51210
D107, D108, D127, D128: BAS21; SOT-23; MPN BAS21,215; LCSC C8661
D147, D148: BAT54; SOT-23; MPN BAT54,215; LCSC C85084
Q107, Q108: MJD350T4G; TO-252-3_TabPin2; MPN MJD350T4G; LCSC C145514
Q117, Q118, Q127, Q128: MMBT3904; SOT-23; MPN MMBT3904(RANGE:100-300); LCSC C20526
Q137, Q138: AO3401A; SOT-23; MPN AO3401A; LCSC C15127
Q157, Q158: MMBT3906; SOT-23; MPN MMBT3906 2A(RANGE:100-300); LCSC C2143
R1180, R1210: 33R; R_0805_2012Metric; MPN 0805W8F330JT5E; LCSC C17634
R1181, R1211: 2.2k; R_0805_2012Metric; MPN 0805W8F2201T5E; LCSC C17520
R1182, R1183, R1202, R1203, R1212, R1213, R1232, R1233: 1k; R_0805_2012Metric; MPN 0805W8F1001T5E; LCSC C17513
R1184, R1185, R1186, R1187, R1214, R1215, R1216, R1217: 100k; R_0805_2012Metric; MPN 0805W8F1003T5E; LCSC C149504
R1188, R1218: 68k; R_0805_2012Metric; MPN 0805W8F6802T5E; LCSC C17801
R1201, R1231: 10k; R_0805_2012Metric; MPN 0805W8F1002T5E; LCSC C17414
U21: LM2902DR; SOIC-14_3.9x8.7mm_P1.27mm; MPN LM2902DR; LCSC C350545

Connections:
+5V_LOGIC: Q137.2 (S), Q138.2 (S), Q157.2 (E), Q158.2 (E), R1180.1, R1183.1, R1188.1, R1202.1, R1210.1, R1213.1, R1218.1, R1232.1; also elsewhere on the board
/14 | Wetting sources 7-8/IN7_AMP_OUT: C137.1, R1181.2, U21.8
/14 | Wetting sources 7-8/IN7_DRV_BASE: Q117.1 (B), R1181.1
/14 | Wetting sources 7-8/IN7_DRV_COL: Q117.3 (C), R1182.2
/14 | Wetting sources 7-8/IN7_UV_GATE: Q127.3 (C), Q137.1 (G), R1188.2
/14 | Wetting sources 7-8/IN7_WET_COLLECTOR: D107.1 (A), Q107.2 (C)
/14 | Wetting sources 7-8/IN8_AMP_OUT: C138.1, R1211.2, U21.14
/14 | Wetting sources 7-8/IN8_DRV_BASE: Q118.1 (B), R1211.1
/14 | Wetting sources 7-8/IN8_DRV_COL: Q118.3 (C), R1212.2
/14 | Wetting sources 7-8/IN8_UV_GATE: Q128.3 (C), Q138.1 (G), R1218.2
/14 | Wetting sources 7-8/IN8_WET_COLLECTOR: D108.1 (A), Q108.2 (C)
CURRENT_REF: D147.1 (A), D148.1 (A), R1201.1, R1231.1; also elsewhere on the board
GND: C167.2, C168.2, Q117.2 (E), Q118.2 (E), Q127.1 (B), Q128.1 (B), R1187.2, R1217.2; also elsewhere on the board
IN7_AMP_REF: C137.2, D147.3 (K), R1201.2, U21.9 (-)
IN7_EMIT_F: U21.10 (+); also elsewhere on the board
IN7_FIELD: D107.3 (K), D127.3 (K); also elsewhere on the board
IN7_LIMIT_BASE: Q157.1 (B), R1202.2, R1203.1
IN7_UV_EMITTER: C167.1, Q127.2 (E), R1184.1, R1187.1; also elsewhere on the board
IN7_WET_BASE: Q107.1 (B), Q137.3 (D), Q157.3 (C), R1182.1, R1183.2
IN7_WET_EMIT: Q107.3 (E), R1180.2, R1203.2; also elsewhere on the board
IN8_AMP_REF: C138.2, D148.3 (K), R1231.2, U21.13 (-)
IN8_EMIT_F: U21.12 (+); also elsewhere on the board
IN8_FIELD: D108.3 (K), D128.3 (K); also elsewhere on the board
IN8_LIMIT_BASE: Q158.1 (B), R1232.2, R1233.1
IN8_UV_EMITTER: C168.1, Q128.2 (E), R1214.1, R1217.1; also elsewhere on the board
IN8_WET_BASE: Q108.1 (B), Q138.3 (D), Q158.3 (C), R1212.1, R1213.2
IN8_WET_EMIT: Q108.3 (E), R1210.2, R1233.2; also elsewhere on the board
unnamed: D127.1 (A), R1186.2
unnamed: D128.1 (A), R1216.2
unnamed: R1184.2, R1185.1
unnamed: R1185.2, R1186.1
unnamed: R1214.2, R1215.1
unnamed: R1215.2, R1216.1

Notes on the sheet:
UNIVERSAL POOFER CONTROL | 14 | Wetting sources 7-8
REV A.3 | Dry contacts | Latched hardware stop | Buffered expansion
INPUT 7 | PRECISION WETTING SOURCE
Nominal 20 mA; compensated servo and backup limiter
AUTONOMOUS NEGATIVE-FAULT CLAMP
INPUT 8 | PRECISION WETTING SOURCE
